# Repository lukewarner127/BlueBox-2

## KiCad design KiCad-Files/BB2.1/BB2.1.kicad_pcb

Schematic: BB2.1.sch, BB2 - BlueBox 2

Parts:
C1, C8, C9, C10, C11: 100n; 0603
C2, C12: 10u; 0603
C3, C4, C5: 22u; 0805
C7: 1n; 0603
D1: BAT760Q; D_SOD-323_HandSoldering
D2: LED_RED; LED_0603
D3: SP0503BAHT; SOT-143-4_SP0503BAHT
J1: JST-2PIN-CONN; JST-2-PIN-PH-CONN; MPN S2B-PH-K-S(LF)(SN); Digi-Key_PN 455-1719-ND
J2: 10118194-0001LF; USB_Micro_B_Female_10118194-0001LF; MPN 10118194-0001LF; Digi-Key_PN 609-4618-1-ND
L1: 1.5u; Murata_Inductor
MOD1: ESP32-WROOM-32; ESP32-WROOM-32D; MPN ESP32-WROOM-32; Digi-Key_PN 1904-1010-1-ND
Q1: DMP3099L; SOT-23-3
Q2, Q3: MMSS8050-H; SOT-23-3
R1, R5, R6: 10k; 0603
R2: 1M; 0603
R3, R7: 2k; 0603
R4: 100k; 0603
U1: TPS63051; VQFN-12_2.5x2.5mm
U2: ISM330DLC; LGA-14L_2.5x3mm__LSM6DS3
U3: CP2102N-A01-GQFN24; QFN-24-1EP_4x4mm_CP2102N

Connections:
CS: MOD1.33, U2.12
DTR: Q3.2, R5.1, U3.23
EN: C8.1, MOD1.3, Q2.3, R1.2
GND: C1.2, C2.2, C3.2, C4.2, C5.2, C7.2, C8.2, C9.2, C10.2, C11.2, C12.2, D2.1, D3.1, J1.2, J2.5, J2.SH, MOD1.1, MOD1.15, MOD1.38, MOD1.39, R4.2, U1.2, U1.6, U1.9, U2.6, U2.7, U3.2, U3.25
INT1: MOD1.9, U2.4
INT2: MOD1.10, U2.9
IO0: MOD1.25, Q3.3
LED: MOD1.24, R3.1
MISO: MOD1.31, U2.1
MOSI: MOD1.37, U2.14
unnamed: C3.1, D1.1, Q1.2 (S), U1.10, U1.11, U1.12
unnamed: C7.1, U1.7
unnamed: D2.2, R3.2
unnamed: L1.1, U1.1
unnamed: L1.2, U1.3
unnamed: Q2.1, R5.2
unnamed: Q3.1, R6.2
unnamed: R2.1, U1.8
unnamed: R7.2, U3.9
RTS: Q2.2, R6.1, U3.19
RXD: MOD1.34, U3.20
SCL: MOD1.30, U2.13
TXD: MOD1.35, U3.21
USB_DN: D3.2, J2.2, U3.4
USB_DP: D3.3, J2.3, U3.3
VBAT: J1.1, Q1.3 (D)
VBUS: D1.2, D3.4, J2.1, Q1.1 (G), R4.1, U3.8
VDD3V3: C1.1, C2.1, C4.1, C5.1, C9.1, C11.1, C12.1, MOD1.2, R1.1, R2.2, R7.1, U1.4, U1.5, U2.8, U3.5, U3.6, U3.7
VDDIO: C10.1, U2.2, U2.3, U2.5

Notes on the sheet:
AUTO PROGRAM DTR RTS <-> EN IO0 1 1 | 1 1 0 0 | 1 1 1 0 | 0 1 0 1 | 1 0
CPU
IMU
USB-UART INTERFACE
AUTO PROGRAM
POWER CONVERSION AND SWITCHOVER

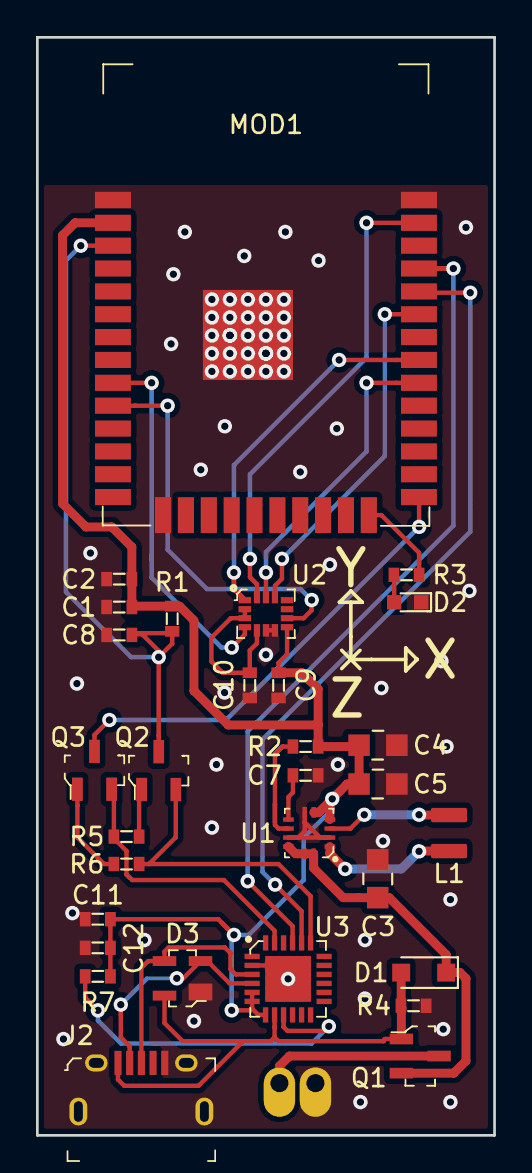
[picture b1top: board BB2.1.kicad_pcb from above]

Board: 2 copper layers, 25.4 x 61.0 mm, 31 parts (1 on the bottom side), 29 nets.

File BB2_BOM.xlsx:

|  |  | Name | Description | Package/Size | Source | Qty | Price | Cost | Link
 |  |  | ESP32 | RF Transciever Module | (25.5x18.0 mm) | Digi-Key | 1 | 7.38 | 7.38 | https://www.digikey.com.au/product-detail/en/espressif-syste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
 |  |  |  | 10k Resistor | 0603 | Digi-Key | 1 | 0.15 | 0.15 | https://www.digikey.com.au/product-detail/en/rohm-semiconduc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
 |  |  |  | 10u Capacitor | 0603 | Digi-Key | 1 | 0.22 | 0.22 | https://www.digikey.com.au/product-detail/en/samsung-electro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
 |  |  |  | 100n Capacitor | 0603 | Digi-Key | 2 | 0.15 | 0.3 | https://www.digikey.com.au/product-detail/en/samsung-electro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
 |  |  |  | Red LED | 0603 | Digi-Key | 1 | 0.22 | 0.22 | https://www.digikey.com.au/product-detail/en/wurth-electroni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
 |  |  |  | 2k Resistor | 0603 | Digi-Key | 1 | 0.15 | 0.15 | https://www.digikey.com.au/product-detail/en/rohm-semiconduc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
 |  |  | ISM330DLC | IMU | LGA-14L (2.5x3.0 mm) | Digi-Key | 1 | 5.94 | 5.94 | https://www.digikey.com.au/product-detail/en/stmicroelectron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
 |  |  |  | 100n Capacitor | 0603 | Digi-Key | 2 | 0.15 | 0.3 | https://www.digikey.com.au/product-detail/en/samsung-electro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
 |  |  | CP2102N | USB to UART Bridge | 24-QFN (4.0x4.0 mm) | Digi-Key | 1 | 2.1 | 2.1 | https://www.digikey.com.au/product-detail/en/silicon-labs/CP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
 |  |  |  | 10u Capacitor | 0603 | Digi-Key | 1 | 0.15 | 0.15 | https://www.digikey.com.au/product-detail/en/samsung-electro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
 |  |  |  | 100n Capacitor | 0603 | Digi-Key | 1 | 0.15 | 0.15 | https://www.digikey.com.au/product-detail/en/samsung-electro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
 |  |  |  | 2k Resistor | 0603 | Digi-Key | 1 | 0.15 | 0.15 | https://www.digikey.com.au/product-detail/en/rohm-semiconduc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
 |  |  | 10118194-0001LF | Micro USB-B Connector |  | Digi-Key | 1 | 0.63 | 0.63 | https://www.digikey.com.au/product-detail/en/amphenol-icc-fc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
 |  |  | SP0503BAHT | TVS Diode Array | SOT-143-4 | Digi-Key | 1 | 1.32 | 1.32 | https://www.digikey.com.au/product-detail/en/littelfuse-inc/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
 |  |  | TPS63051 | Buck-Boost Converter | VQFN (12) 2.5x2.5 mm | Digi-Key | 1 | 2.82 | 2.82 | https://www.digikey.com.au/product-detail/en/texas-instrumen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
 |  |  | 1239AS-H-1R5M | 1.5u Inductor | 1008 | Digi-Key | 1 | 0.63 | 0.63 | https://www.digikey.com.au/product-detail/en/murata-electron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
 |  |  |  | 22u Capacitor | 0805 | Digi-Key | 3 | 0.27 | 0.81 | https://www.digikey.com.au/product-detail/en/samsung-electro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
 |  |  |  | 1n Capacitor | 0603 | Digi-Key | 1 | 0.15 | 0.15 | https://www.digikey.com.au/product-detail/en/samsung-electro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
 |  |  |  | 1M Resistor | 0603 | Digi-Key | 1 | 0.15 | 0.15 | https://www.digikey.com.au/product-detail/en/rohm-semiconduc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
 |  |  | JST 2-Pin Connector | Battery connector |  | Digi-Key | 1 | 0.25 | 0.25 | https://www.digikey.com.au/product-detail/en/jst-sales-ameri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
 |  |  | BAT760Q | Schottky Diode | SOD-323 | Digi-Key | 1 | 0.63 | 0.63 | https://www.digikey.com.au/product-detail/en/diodes-incorpor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
 |  |  | DMP3099L | P-Channel Mosfet | SOT-23 | Digi-Key | 1 | 0.49 | 0.49 | https://www.digikey.com.au/product-detail/en/diodes-incorpor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
 |  |  |  | 100k Resistor | 0603 | Digi-Key | 1 | 0.15 | 0.15 | https://www.digikey.com.au/product-detail/en/rohm-semiconduc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
 |  |  |  | 10k Resistor | 0603 | Digi-Key | 2 | 0.15 | 0.3 | https://www.digikey.com.au/product-detail/en/rohm-semiconduc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
 |  |  | SS8050 | NPN Transistor | SOT-23 | Digi-Key | 2 | 0.31 | 0.62 | https://www.digikey.com.au/product-detail/en/micro-commercia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
 |  |  | LiPo Battery | 400 mAh Pouch Cell | 38x25x6 mm | Core Electronics | 1 | 10.95 | 10.95 | https://core-electronics.com.au/polymer-lithium-ion-battery-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
 |  |  |  |  |  |  |  |  | 0
 |  |  |  |  |  |  |  |  | 0
 |  |  |  |  |  |  |  |  | 0
 |  |  |  |  |  |  |  |  | 0
 |  |  |  |  |  |  |  |  | 37.109999999999992

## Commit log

2019-10-13 Rename BB2_v1.0 to BB2_v1.0.ino
2019-10-19 Rename BB2_7.ino.ino to BB2_1.ino
2019-10-19 Coding in progress
2019-10-19 Current working version
